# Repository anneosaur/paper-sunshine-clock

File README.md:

# paper sunshine clock

This project is a clock that tells time in a unique way. The face of the display looks like the sun with 12 rays representing 12 o’clock to 11 o’clock, going clockwise, which turn from black to yellow as each hour passes. Each ray is divided up into half hour segments, so the clock is able to tell you the current half hour. For example in the photo above, the clock is reading between 9 o’clock and 9:30. The display is made out of paper and uses thermochromic paint which changes color with heat. There is a thin circuit board behind the paper which provides the warmth to activate the thermochromic paint, changing the colors of the rays. The clock also has Sparkle Mode, which will turn on a random ray every 10 seconds. It provides an entertaining show as the rays turn on and fade away (see [Videos](#Videos) below).

https://github.com/user-attachments/assets/e0f1c668-d030-4747-b99e-f9c4dc16aae8

---
### How to read the clock

---
### How it works
The clock works by using thermochromic paint screen printed onto a piece of Japanese awagami paper. Behind that, is a flex PCB with large resistors mounted on the back. These resistors can be selectively turned on, warming up the paper and activating the thermochromic paint. 
Each ray on the PCB is a copper pour used to spread and hold heat from the resistors. It was designed using Python and an SVG drawing library, and converted into a KiCad footprint.

The control board is driven by an Atmega328PB and uses a RV-3028 RTC for accurate time keeping. Supercapacitors are used to provide backup power for the RTC, allowing the clock to keep track of time when it is powered off. The time is initially set when programming the clock, and can be changed in +/- 30 minute increments using the two buttons on the back.

It uses a multiplexing system which allows the 24 segments to be controlled with 10 connections. The rays of the clock are divided in 3 groups, with 4 rays each. Each group has a top and bottom ground connection connecting the rays (allowing the half hour segments to be individually controlled). The “similar” rays of each group (e.g., the first ray of each group, the second ray of each group, etc) have a shared 5v connection. So for example, to turn on the segment representing the first half hour of 12 o’clock, ground the bottom connection of the first group and apply 5v to the first ray.

For safety (since we’re applying heat to paper here), I used an eFuse to clamp the input voltage at 5v. There are also SMD fuses to prevent each segment from getting too much current. 

In order to keep the rays at the proper temperature to activate the thermochromic paint (around 90-100 F / 32-38 C), a temperature sensor reads the ambient temperature and will PWM the display to maintain a reasonably consistent temperature. This actually got a bit complicated, since the heat from the display would warm up the back compartment where the control PCB is and influence the temperature sensor. Fortunately, the temperature increases were fairly predicable and could be compensated for. From testing, the clock works well in room temperatures between 65-80 F / 18-27 C.

The enclosure was designed in OpenSCAD and is 3D printed.

# Videos

[Startup sequence](https://www.youtube.com/watch?v=sf5E_oBU3c0)

[5 minutes of Sparkle Mode in real time](https://www.youtube.com/watch?v=p_eX9BhE4EM)

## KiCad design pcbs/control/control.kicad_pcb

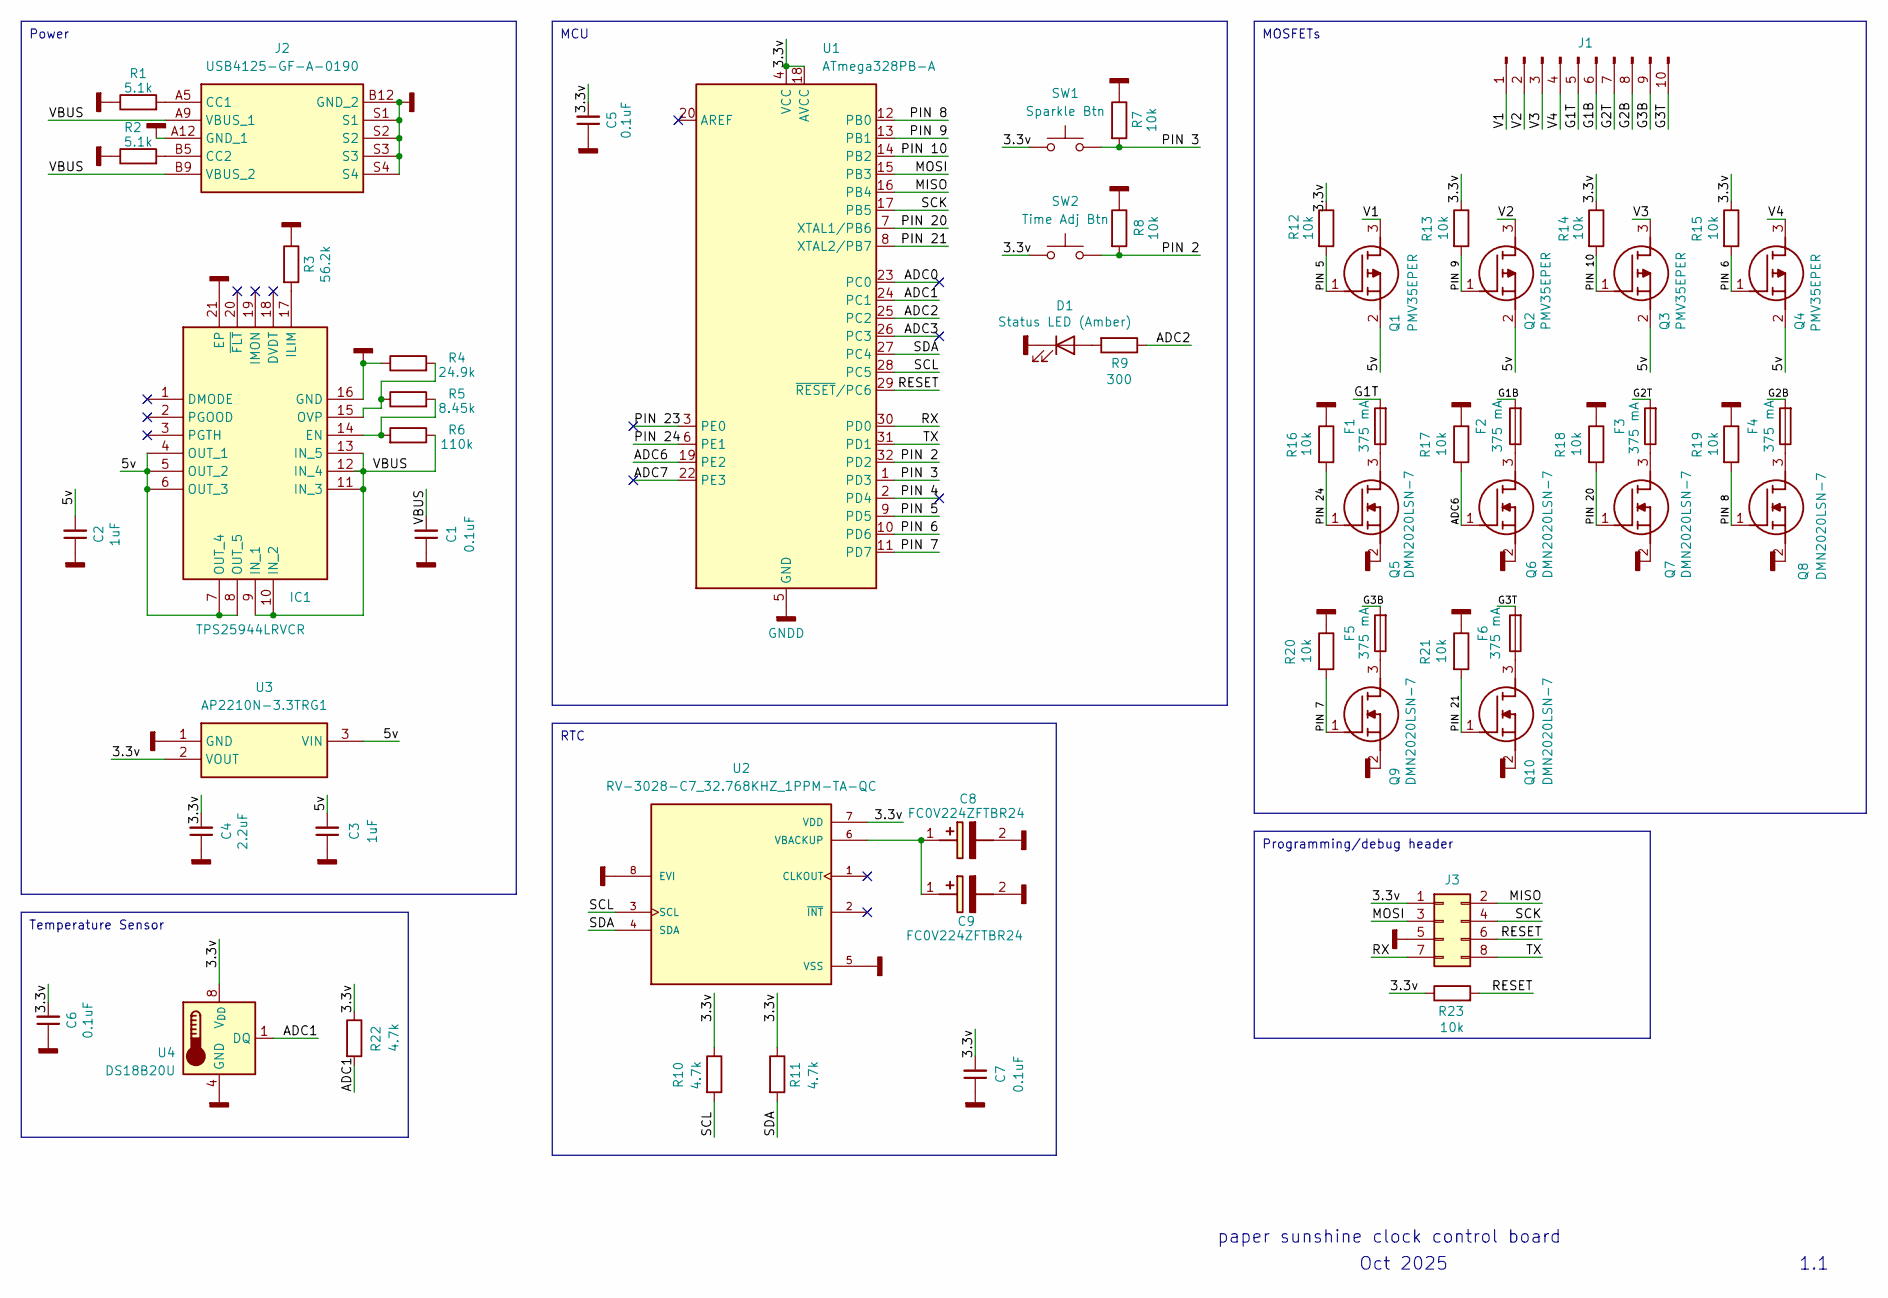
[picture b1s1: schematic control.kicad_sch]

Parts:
C1, C5, C6, C7: 0.1uF; C_0805_2012Metric
C2, C3: 1uF; C_0805_2012Metric
C4: 2.2uF; C_0805_2012Metric
C8, C9: FC0V224ZFTBR24; CAPAE1080X550N; Mouser Part Number 80-FC0V224ZFTBR24
D1: Status LED (Amber); LED_0805_2012Metric
F1, F2, F3, F4, F5, F6: 375 mA; Fuse_0603_1608Metric
IC1: TPS25944LRVCR; QFN50P300X400X80-21N; Mouser Part Number 595-TPS25944LRVCR
J1: Conn_01x10_Pin; CON10_SMT-RA_FCC-FPC2
J2: USB4125-GF-A-0190; GCT_USB4125-GF-A-0190_REVA2; Manufacturer_Part_Number USB4125-GF-A-0190; Mouser Part Number 640-USB4125-GF-A-190
J3: Conn_02x04_Odd_Even; PinHeader_2x04_P1.27mm_Vertical
Q1: PMV35EPER; SOT95P237X112-3N; Manufacturer_Part_Number SI2393DS-T1-GE3; Mouser Part Number 78-SI2393DS-T1-GE3
Q2, Q3, Q4: PMV35EPER; SOT95P237X112-3N; Mouser Part Number 78-SI2393DS-T1-GE3
Q5, Q6, Q7, Q8, Q9, Q10: DMN2020LSN-7; SOT95P285X130-3N; Mouser Part Number 621-DMN2020LSN-7
R1, R2: 5.1k; R_0805_2012Metric
R3: 56.2k; R_0805_2012Metric
R4: 24.9k; R_0805_2012Metric
R5: 8.45k; R_0805_2012Metric
R6: 110k; R_0805_2012Metric
R7, R8, R12, R13, R14, R15, R16, R17, R18, R19, R20, R21, R23: 10k; R_0805_2012Metric
R9: 300; R_0805_2012Metric
R10, R11, R22: 4.7k; R_0805_2012Metric
SW1: Sparkle Btn; SW_PUSH_6mm
SW2: Time Adj Btn; SW_PUSH_6mm
U1: ATmega328PB-A; TQFP-32_7x7mm_P0.8mm
U2: RV-3028-C7_32.768KHZ_1PPM-TA-QC; IC_RV-3028-C7_32.768KHZ_1PPM-TA-QC; PARTREV 1.3
U3: AP2210N-3.3TRG1; SOT95P282X145-3N; Manufacturer_Part_Number AP2210N-3.3TRG1; Mouser Part Number 621-AP2210N-3.3TRG1
U4: DS18B20U; MSOP-8_3x3mm_P0.65mm

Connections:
/3.3v: C4.2, C5.2, C6.2, C7.2, J3.1, R10.1, R11.1, R12.1, R13.1, R14.1, R15.1, R22.1, R23.1, SW1.1, SW2.1, U1.4 (VCC), U1.18 (AVCC), U2.7 (VDD), U3.2 (VOUT), U4.8 (V_{DD})
/5v: C2.2, C3.2, IC1.4 (OUT_1), IC1.5 (OUT_2), IC1.6 (OUT_3), IC1.7 (OUT_4), IC1.8 (OUT_5), Q1.2 (S), Q2.2 (S), Q3.2 (S), Q4.2 (S), U3.3 (VIN)
/ADC0: U1.23 (PC0)
/ADC1: R22.2, U1.24 (PC1), U4.1 (DQ)
/ADC2: R9.1, U1.25 (PC2)
/ADC3: U1.26 (PC3)
/ADC6: Q6.1 (G), R17.2, U1.19 (PE2)
/ADC7: U1.22 (PE3)
/G1B: F2.2, J1.6
/G1T: F1.2, J1.5
/G2B: F4.2, J1.8
/G2T: F3.2, J1.7
/G3B: F5.2, J1.9
/G3T: F6.2, J1.10
/MISO: J3.2, U1.16 (PB4)
/MOSI: J3.3, U1.15 (PB3)
/PIN 2: R8.2, SW2.2, U1.32 (PD2)
/PIN 3: R7.2, SW1.2, U1.1 (PD3)
/PIN 4: U1.2 (PD4)
/PIN 5: Q1.1 (G), R12.2, U1.9 (PD5)
/PIN 6: Q4.1 (G), R15.2, U1.10 (PD6)
/PIN 7: Q9.1 (G), R20.2, U1.11 (PD7)
/PIN 8: Q8.1 (G), R19.2, U1.12 (PB0)
/PIN 9: Q2.1 (G), R13.2, U1.13 (PB1)
/PIN 10: Q3.1 (G), R14.2, U1.14 (PB2)
/PIN 20: Q7.1 (G), R18.2, U1.7 (XTAL1/PB6)
/PIN 21: Q10.1 (G), R21.2, U1.8 (XTAL2/PB7)
/PIN 23: U1.3 (PE0)
/PIN 24: Q5.1 (G), R16.2, U1.6 (PE1)
/RESET: J3.6, R23.2, U1.29 (~RESET/PC6)
/RX: J3.7, U1.30 (PD0)
/SCK: J3.4, U1.17 (PB5)
/SCL: R10.2, U1.28 (PC5), U2.3 (SCL)
/SDA: R11.2, U1.27 (PC4), U2.4 (SDA)
/TX: J3.8, U1.31 (PD1)
/V1: J1.1, Q1.3 (D)
/V2: J1.2, Q2.3 (D)
/V3: J1.3, Q3.3 (D)
/V4: J1.4, Q4.3 (D)
/VBUS: C1.2, IC1.9 (IN_1), IC1.10 (IN_2), IC1.11 (IN_3), IC1.12 (IN_4), IC1.13 (IN_5), J2.A9 (VBUS_1), J2.B9 (VBUS_2), R6.1
GNDD: C1.1, C2.1, C3.1, C4.1, C5.1, C6.1, C7.1, C8.2 (-), C9.2 (-), D1.1 (K), IC1.16 (GND), IC1.21 (EP), J2.A12 (GND_1), J2.B12 (GND_2), J2.S1, J2.S2, J2.S3, J2.S4, J3.5, Q5.2 (S), Q6.2 (S), Q7.2 (S), Q8.2 (S), Q9.2 (S), Q10.2 (S), R1.1, R2.1, R3.1, R4.1, R7.1, R8.1, R16.1, R17.1, R18.1, R19.1, R20.1, R21.1, U1.5 (GND), U1.21 (GND), U2.5 (VSS), U2.8 (EVI), U3.1 (GND), U4.4 (GND)
unnamed: C8.1 (+), C9.1 (+), U2.6 (VBACKUP)
unnamed: D1.2 (A), R9.2
unnamed: IC1.14 (EN), R5.2, R6.2
unnamed: IC1.17 (ILIM), R3.2
unnamed: IC1.15 (OVP), R4.2, R5.1
unnamed: J2.A5 (CC1), R1.2
unnamed: J2.B5 (CC2), R2.2
unnamed: F1.1, Q5.3 (D)
unnamed: F2.1, Q6.3 (D)
unnamed: F3.1, Q7.3 (D)
unnamed: F4.1, Q8.3 (D)
unnamed: F5.1, Q9.3 (D)
unnamed: F6.1, Q10.3 (D)

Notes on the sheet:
MOSFETs
RTC
Power
Temperature Sensor
Programming/debug header
MCU
1.1
Oct 2025
paper sunshine clock control board

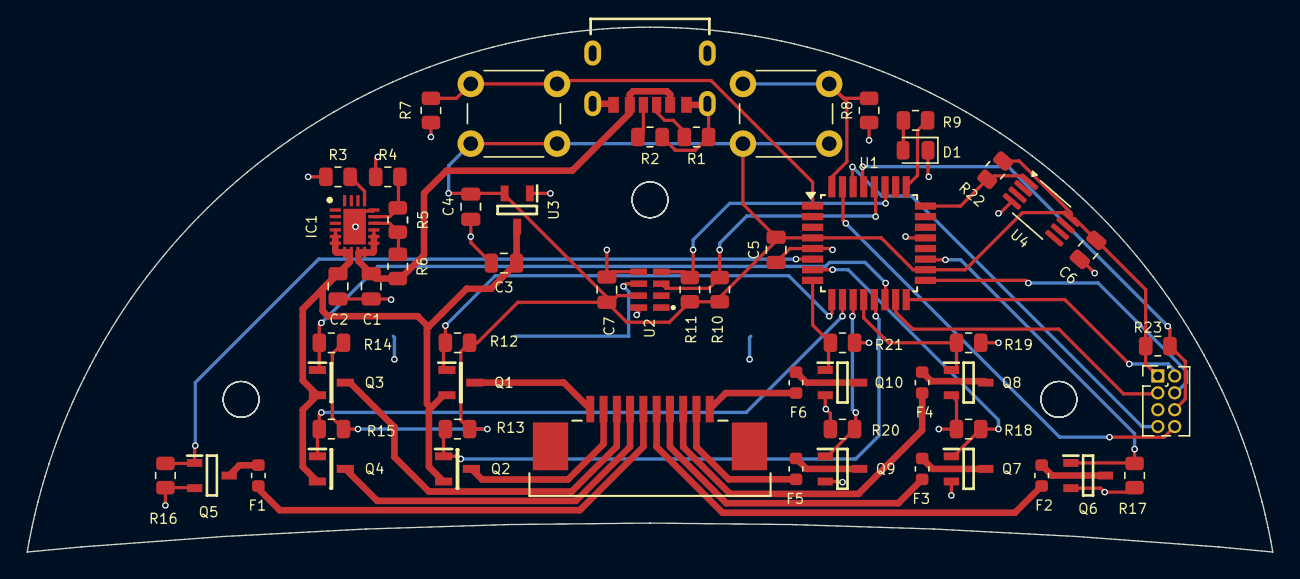
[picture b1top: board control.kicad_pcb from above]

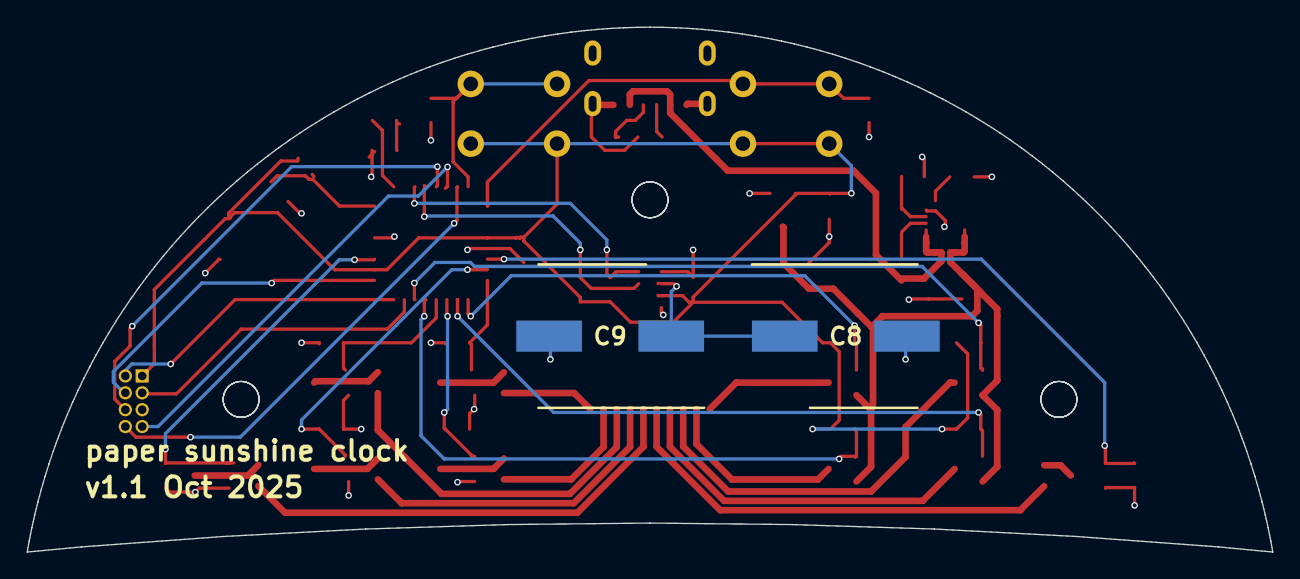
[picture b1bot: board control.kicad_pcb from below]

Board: 4 copper layers, 93.8 x 39.5 mm, 60 parts (2 on the bottom side), 49 nets.

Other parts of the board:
Ref**: Val**; control_pcb_outline

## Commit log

2025-03-09 added to version control
2025-06-01 pcb and enclosure update
2025-06-07 enclosure update
2025-06-08 lengthened display cable
2025-06-08 enclosure parameter improvement
2025-06-14 changed top retaining clip value
2025-10-03 rv-3028 board
